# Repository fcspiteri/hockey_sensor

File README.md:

# Hockey Sensor (`HKS`) — Chest-Worn Indoor Ice Hockey Player Tracking System

Production-grade hardware, firmware, and host sensor-fusion suite for a discrete chest-worn indoor ice hockey player tracker (`52.0 × 36.0 × 10.5 mm`, `24.0 g`, IP67) operating **without GPS/GNSS or external rink-side anchors/beacons**.

## Tracked Metrics
- **2D On-Ice Position (`x_m`, `y_m`) & Trajectory Reconstruction** in Rink Frame $R$ (`60.96 × 25.91 m` NHL or `60.0 × 30.0 m` IIHF)
- **Skating Speed & Peak/Mean Speed** (`m/s`, `km/h`)
- **3-Axis Linear Acceleration & High-$g$ Impact Events** ($\pm 16\,g$ strapdown + $\pm 200\,g$ check/impact capture)
- **Shift Detection, On-Ice vs. Bench Gating & Shift Length** (`s`)
- **Total & Per-Shift Distance Skated** (`m`)

---

## Hardware & Industrial Design Renders

### 1. Chest-Worn Enclosure Concept (`52.0 × 36.0 × 10.5 mm`, `24.0 g`, IP67)

### 2. Exploded Assembly Stack-Up (`BT1` 502535 450 mAh LiPo Battery Underneath PCBA)

### 3. Populated 4-Layer PCBA Concept (`38.0 × 28.0 × 0.80 mm`)

### 4. Bare 4-Layer FR4 ENIG PCB Concept & KiCad 3D Raytraced Layout
| Bare 4-Layer PCB Concept | KiCad 3D Raytraced Routed PCB |
| :---: | :---: |
|  |  |

---

## Sample Session Telemetry & Sensor Fusion Output
| Raw Sensor Telemetry (`ICM-42688`, `ADXL372`, `MMC5983MA`, `BMP581`) | Fused Speed, Shifts, Distance & Acceleration |
| :---: | :---: |
|  |  |

---

## Repository Structure

| Path | Description |
| :--- | :--- |
| [`PROJECT_SPEC.md`](PROJECT_SPEC.md) | System requirements, coordinate frames ($R, B, S$), budgets, and validation gates |
| [`INTERFACE_CONTRACT.json`](INTERFACE_CONTRACT.json) | Single source of truth for `.hks` binary flash format, USB/BLE protocol, pinmux, and JSON output schema |
| [`docs/`](docs/) | System architecture (`architecture.md`), contract validator (`validate_contract.py`), and sample telemetry plots (`docs/plots/`) |
| [`hardware/ee/`](hardware/ee/) | Detailed schematic design (`schematic_design.md`), nRF5340 pinmux (`pinmux_and_buses.json`), and EE BOM (`bom.csv`) |
| [`hardware/mechanical/`](hardware/mechanical/) | IP67 PC/TPU + LSR overmolded chest pod specification (`enclosure_spec.md`), dimensions (`dimensions.json`), and mechanical BOM (`bom.csv`) |
| [`hardware/kicad/`](hardware/kicad/) | Routed 4-layer KiCad 8/10 project (`hockey_sensor.kicad_pro`, `hockey_sensor.kicad_sch`, `hockey_sensor.kicad_pcb`), Specctra DSN/SES (`board.dsn`, `board.ses`), DRC report (`drc_report.json`), and turnkey JLCPCB/PCBWay production files (`production/`) |
| [`hardware/power_budget.py`](hardware/power_budget.py) | $0\,^\circ\text{C}$ LiPo battery runtime, flash storage, and mass budget verifier |
| [`firmware/`](firmware/) | Freestanding C11 firmware suite (`libhks_fw.a`), 4096-byte NAND page logger, CRC-32C/SHA-256 integrity, USB CDC-ACM / BLE 5.3 transfer engine, and CLI simulator |
| [`sim/`](sim/) | 400 Hz skating physics truth generator (`physics_sim.py`), `.hks` binary codec (`flash_codec.py`), USB/BLE downloader (`downloader.py`), and 6-layer Error-State EKF + RTS backward smoother (`fusion_pipeline.py`) |
| [`e2e/`](e2e/) | 151-test end-to-end verification suite and 21-check 5-pillar production-readiness rubric (`run_e2e.py`) |

---

## Quick Start & Verification

```zsh
# 1. Validate interface contract & schema parity (27 checks)
python3 docs/validate_contract.py

# 2. Run hardware power, mass, storage, and pinmux unit tests (8 tests)
python3 -m unittest discover -s hardware/tests -v

# 3. Build and test freestanding C11 firmware (13 tests)
make -C firmware test

# 4. Run Python simulation & 6-layer ES-EKF + RTS fusion unit tests (8 tests)
python3 -m unittest discover -s sim/tests -v

# 5. Run full end-to-end test suite & 5-pillar rubric (151 tests, 21 rubric checks)
python3 e2e/run_e2e.py
```

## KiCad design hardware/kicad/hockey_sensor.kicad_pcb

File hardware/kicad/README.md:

# `hockey_sensor` — KiCad 8 Project & Turnkey PCBA Files

This directory contains the generated **KiCad 8/9** design files and turnkey SMT assembly outputs derived directly from [`../ee/schematic_design.md`](../ee/schematic_design.md), [`../ee/pinmux_and_buses.json`](../ee/pinmux_and_buses.json), [`../ee/bom.csv`](../ee/bom.csv), and [`../mechanical/dimensions.json`](../mechanical/dimensions.json).

## Generated Files

| File | Description |
| :--- | :--- |
| [`hockey_sensor.kicad_pro`](./hockey_sensor.kicad_pro) | KiCad 8 project with 4-layer design rules (`0.09 mm` track/space for `aQFN-94`, `90 Ω` USB diff pair, `50 Ω` RF GCPW) |
| [`hockey_sensor.kicad_sch`](./hockey_sensor.kicad_sch) | KiCad 8 schematic (`Eeschema`) containing all 54 component instances (`U1`–`U10`, `J1`, `J2`, `A1`, `Y1`, `Y2`, `L1`–`L6`, `Q1`, `LD1`, `LD2`, `D1`, `D2`, `SW1`, `BT1`, `RT1`, resistors, and capacitors) |
| [`hockey_sensor.kicad_pcb`](./hockey_sensor.kicad_pcb) | KiCad 8 4-layer PCB (`Pcbnew`, `38.0 × 28.0 × 0.80 mm`, ENIG finish) with `Edge.Cuts`, `8.0 × 8.0 mm` 4-layer RF keepout, `M1.4` mounting holes, `In1.Cu`/`B.Cu` `GND` planes, `In2.Cu` `1.8 V` plane, and placed top-side footprints aligned to Sensor Frame `S` ($R_{BS}$) |
| [`hockey_sensor.net`](./hockey_sensor.net) | Complete KiCad S-expression netlist (`64` nets across all isolated SPI/I2C/QSPI/USB/PMIC buses) |
| [`production/hockey_sensor_pcba_bom.csv`](./production/hockey_sensor_pcba_bom.csv) | Turnkey PCBA Bill of Materials formatted for JLCPCB / PCBWay / MacroFab |
| [`production/hockey_sensor_cpl_pick_and_place.csv`](./production/hockey_sensor_cpl_pick_and_place.csv) | Centroid Pick-and-Place (`CPL`) coordinates (`Mid X`, `Mid Y`, `Frame_S_X`, `Frame_S_Y`, `Rotation`, `Layer=top`) |

## How to Open & Route in KiCad 8 / 9

1. Open `hardware/kicad/hockey_sensor.kicad_pro` in **KiCad 8.0+**.
2. Open **PCB Editor (`Pcbnew`)** (`hockey_sensor.kicad_pcb`):
   - Press **`B`** to fill the `In1.Cu` (`GND`), `In2.Cu` (`VDD_1V8`), and `B.Cu` (`GND_SHIELD`) copper zones (they automatically void around the `8.0 × 8.0 mm` top-right RF keepout under `A1`).
   - Route the fanout tracks using the pre-assigned net classes (`0.09–0.12 mm` for `aQFN-94` signal breakout, `0.22 mm / 0.15 mm` differential pair for `USB_D_P`/`USB_D_N`, `0.32 mm` `50 Ω` GCPW for `RF_ANT_OUT` $	o$ `C_RF1`/`L5`/`L6` $	o$ `A1`).
3. Run **Inspect $	o$ Design Rules Checker (DRC)** and export Gerbers + Drill files via **File $	o$ Fabrication Outputs**.

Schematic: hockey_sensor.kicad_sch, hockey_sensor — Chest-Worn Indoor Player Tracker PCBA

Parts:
A1: 2450AT18B0100001E; Johanson_2450AT18B100; MPN 2450AT18B0100001E
BT1: 502535-450mAh-LiPo-Pads; Battery_Pads_3Pin_VBAT_NTC_GND; MPN 502535-450mAh-LiPo
C1, C2, C3, C4, C5, C6, C7, C8, C9, C10, C11, C12, C13, C14, C15, C16, C17, C18: 100nF_10V; C_0402_1005Metric; MPN GRM155R61A104KA01D
C19: 4.7uF_25V_VBUS; C_0603_1608Metric; MPN GRM188R61E475KE11D
C20: 10uF_6.3V_BUCK1; C_0603_1608Metric; MPN GRM188R60J106ME47D
C21: 10uF_6.3V_BUCK2; C_0603_1608Metric; MPN GRM188R60J106ME47D
C22: 4.7uF_10V_DECUSB; C_0603_1608Metric; MPN GRM188R61A475KE15D
C23: 4.7uF_10V_VDD; C_0603_1608Metric; MPN GRM188R61A475KE15D
C24: 4.7uF_10V_DECD; C_0603_1608Metric; MPN GRM188R61A475KE15D
C25: 4.7uF_10V_DECR; C_0603_1608Metric; MPN GRM188R61A475KE15D
C26: 4.7uF_10V_DECA; C_0603_1608Metric; MPN GRM188R61A475KE15D
C27: 1.2pF_C_RF1; C_0402_1005Metric; MPN GJM1555C1H1R2WB01D
C28: 0.8pF_C_RF_SHUNT_DNI; C_0402_1005Metric; MPN GJM1555C1HR80WB01D; not fitted
D1: ESD5Z5.0T1G; D_SOD-523; MPN ESD5Z5.0T1G
D2: BAT54WS; D_SOD-323; MPN BAT54WS
J1: USB4720-03-A; USB_C_Receptacle_GCT_USB4720-03-A_IP67; MPN USB4720-03-A
J2: TC2050-IDC-NL; Tag-Connect_TC2050-IDC-NL_2x05_P1.27mm_Vertical; MPN TC2050-IDC-NL; not fitted
L1, L2: 2.2uH_DFE201610E-2R2M; L_2016_2016Metric; MPN DFE201610E-2R2M
L3: 10uH_LQM18DN100M70L; L_0603_1608Metric; MPN LQM18DN100M70L
L4: 10uH_LQM18DN100M70L; L_0603_1608Metric_Vert; MPN LQM18DN100M70L
L5: 2.7nH_LQW15AN2N7C00D; L_0402_1005Metric_Vert; MPN LQW15AN2N7C00D
L6: 3.3nH_LQW15AN3N3C00D; L_0402_1005Metric; MPN LQW15AN3N3C00D
LD1: LTST-C191KGKT; LED_0603_1608Metric; MPN LTST-C191KGKT
LD2: LTST-C191KRKT; LED_0603_1608Metric; MPN LTST-C191KRKT
MH1, MH2, MH3, MH4: M1.4_Boss; MountingHole_1.5mm_M1.4; MPN M1.4_Boss_NPTH; not fitted
Q1: NTZD3154NT1G; SOT-563; MPN NTZD3154NT1G
R1: 47k_1%_VSET1; R_0402_1005Metric; MPN ERJ-2RKF4702X
R2: 150k_1%_VSET2; R_0402_1005Metric; MPN ERJ-2RKF1503X
R3: 5.1k_1%_CC1; R_0402_1005Metric; MPN ERJ-2RKF5101X
R4: 5.1k_1%_CC2; R_0402_1005Metric; MPN ERJ-2RKF5101X
R5: 4.7k_I2C0_SDA; R_0402_1005Metric; MPN ERJ-2GEJ472X
R6: 4.7k_I2C0_SCL; R_0402_1005Metric; MPN ERJ-2GEJ472X
R7: 4.7k_I2C2_SDA; R_0402_1005Metric; MPN ERJ-2GEJ472X
R8: 4.7k_I2C2_SCL; R_0402_1005Metric; MPN ERJ-2GEJ472X
R9: 10k_CS_IMU; R_0402_1005Metric; MPN ERJ-2GEJ103X
R10: 10k_CS_HIGHG; R_0402_1005Metric; MPN ERJ-2GEJ103X
R11: 10k_CS_FLASH; R_0402_1005Metric; MPN ERJ-2GEJ103X
R12: 100k_GATE_G; R_0402_1005Metric; MPN ERJ-2GEJ104X
R13: 100k_GATE_R; R_0402_1005Metric; MPN ERJ-2GEJ104X
R14: 100k_BTN_PU; R_0402_1005Metric; MPN ERJ-2GEJ104X
R15: 4.7k_3V0_SDA; R_0402_1005Metric; MPN ERJ-2GEJ472X
R16: 4.7k_3V0_SCL; R_0402_1005Metric; MPN ERJ-2GEJ472X
R17: 200k_PCA_EN; R_0402_1005Metric; MPN ERJ-2GEJ204X
R18: 1k_LED_G; R_0402_1005Metric; MPN ERJ-2GEJ102X
R19: 1k_LED_R; R_0402_1005Metric; MPN ERJ-2GEJ102X
RT1: 10k_NTC_DNI; R_0402_1005Metric; MPN NCP15XH103F03RC; not fitted
SW1: EVPAWCD4A; SW_SPST_EVPAW; MPN EVPAWCD4A
U1: nRF5340-QKAA; Nordic_AQFN-94-1EP_7x7mm_P0.4mm; MPN nRF5340-QKAA-R7
U2: nPM1300-QEAA-R; QFN-32-1EP_5x5mm_P0.5mm; MPN nPM1300-QEAA-R
U3: ICM-42688-P; LGA-14_2.5x3.0mm_P0.5mm; MPN ICM-42688-P
U4: ADXL372BCCZ-RL7; LGA-16_3.0x3.25mm_P0.5mm; MPN ADXL372BCCZ-RL7
U5: MMC5983MA; LGA-16_3.0x3.0mm_P0.5mm; MPN MMC5983MA
U6: BMP581; LGA-10_2.0x2.0mm_P0.5mm; MPN BMP581
U7: W25N01JWZEIG; WSON-8-1EP_8x6mm_P1.27mm; MPN W25N01JWZEIG
U8: PCA9306DCUR; VSSOP-8_2.3x2mm_P0.5mm; MPN PCA9306DCUR
U9: SN74AXC1T45DRLR; SOT-563; MPN SN74AXC1T45DRLR
U10: TPD4E05U06DQAR; USON-10_2.5x1.0mm_P0.5mm; MPN TPD4E05U06DQAR
Y1: NX2016SA-32MHz; Crystal_SMD_2016-4Pin_2.0x1.6mm; MPN NX2016SA-32MHz
Y2: FC-12M-32.768K-20ppm; Crystal_SMD_2012-2Pin_2.0x1.2mm; MPN FC-12M-32.768K-20ppm

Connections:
/ADXL_BYP: C14.1 (ADXL_BYP), U4.2 (ADXL_BYP)
/ADXL_INT1_P0.06: U1.AB2 (ADXL_INT1_P0.06), U4.11 (ADXL_INT1_P0.06)
/ADXL_INT2_P0.07: U1.AD2 (ADXL_INT2_P0.07), U4.9 (ADXL_INT2_P0.07)
/BARO_INT_P1.04: U1.AL19 (BARO_INT_P1.04), U6.7 (BARO_INT_P1.04)
/BTN_USER_N_P1.06: D2.2 (BTN_USER_N_P1.06), R14.1 (BTN_USER_N_P1.06), U1.AL21 (BTN_USER_N_P1.06)
/DECA: C26.1 (DECA), U1.A13 (DECA)
/DECD: C24.1 (DECD), L3.2 (DECD), U1.A15 (DECD)
/DECN: C1.1 (DECN), U1.A23 (DECN)
/DECR: C25.1 (DECR), L4.2 (DECR), U1.A27 (DECR)
/DECRF: C2.1 (DECRF), U1.G31 (DECRF)
/DECUSB: C22.1 (DECUSB), U1.B6 (DECUSB)
/GND: BT1.3 (GND), C1.2 (GND), C2.2 (GND), C3.2 (GND), C4.2 (GND), C5.2 (GND), C6.2 (GND), C7.2 (GND), C8.2 (GND), C9.2 (GND), C10.2 (GND), C11.2 (GND), C12.2 (GND), C13.2 (GND), C14.2 (GND), C15.2 (GND), C16.2 (GND), C17.2 (GND), C18.2 (GND), C19.2 (GND), C20.2 (GND), C21.2 (GND), C22.2 (GND), C23.2 (GND), C24.2 (GND), C25.2 (GND), C26.2 (GND), C28.1 (GND), D1.2 (GND), J1.A1 (GND), J1.B1 (GND), J1.S1 (GND), J1.S2 (GND), J2.3 (GND), J2.5 (GND), J2.9 (GND), L5.2 (GND), Q1.1 (GND), Q1.4 (GND), R1.2 (GND), R2.2 (GND), R3.2 (GND), R4.2 (GND), R12.2 (GND), R13.2 (GND), RT1.2 (GND), SW1.2 (GND), U1.A25 (GND), U1.AG31 (GND), U1.B12 (GND), U1.B26 (GND), U1.D2 (GND), U1.EP (GND), U1.F2 (GND), U1.G1 (GND), U1.H2 (GND), U1.J31 (GND), U1.K2 (GND), U1.T2 (GND), U2.2 (GND), U2.6 (GND), U2.EP (GND), U3.6 (GND), U3.7 (GND), U3.10 (GND), U3.11 (GND), U4.5 (GND), U4.12 (GND), U4.13 (GND), U4.15 (GND), U5.6 (GND), U5.9 (GND), U5.11 (GND), U6.3 (GND), U6.8 (GND), U6.9 (GND), U7.4 (GND), U7.9 (GND), U8.1 (GND), U9.2 (GND), U9.5 (GND), U10.3 (GND), U10.8 (GND), Y1.2 (GND), Y1.4 (GND)
/HFXO_XC1: U1.C31 (HFXO_XC1), Y1.1 (HFXO_XC1)
/HFXO_XC2: U1.B30 (HFXO_XC2), Y1.3 (HFXO_XC2)
/I2C0_SCL_1V8_P1.03: R6.1 (I2C0_SCL_1V8_P1.03), U1.AF2 (I2C0_SCL_1V8_P1.03), U6.2 (I2C0_SCL_1V8_P1.03), U8.3 (I2C0_SCL_1V8_P1.03)
/I2C0_SCL_3V0: R16.1 (I2C0_SCL_3V0), U5.1 (I2C0_SCL_3V0), U8.6 (I2C0_SCL_3V0)
/I2C0_SDA_1V8_P1.02: R5.1 (I2C0_SDA_1V8_P1.02), U1.AE1 (I2C0_SDA_1V8_P1.02), U6.4 (I2C0_SDA_1V8_P1.02), U8.4 (I2C0_SDA_1V8_P1.02)
/I2C0_SDA_3V0: R15.1 (I2C0_SDA_3V0), U5.5 (I2C0_SDA_3V0), U8.5 (I2C0_SDA_3V0)
/I2C2_PMIC_SCL_P0.24: R8.1 (I2C2_PMIC_SCL_P0.24), U1.AL27 (I2C2_PMIC_SCL_P0.24), U2.14 (I2C2_PMIC_SCL_P0.24)
/I2C2_PMIC_SDA_P0.23: R7.1 (I2C2_PMIC_SDA_P0.23), U1.AK20 (I2C2_PMIC_SDA_P0.23), U2.13 (I2C2_PMIC_SDA_P0.23)
/IMU_INT1_P0.04: U1.V2 (IMU_INT1_P0.04), U3.4 (IMU_INT1_P0.04)
/IMU_INT2_P0.05: U1.Y2 (IMU_INT2_P0.05), U3.9 (IMU_INT2_P0.05)
/LED_G_ANODE: LD1.1 (LED_G_ANODE), R18.2 (LED_G_ANODE)
/LED_G_CATHODE: LD1.2 (LED_G_CATHODE), Q1.6 (LED_G_CATHODE)
/LED_G_GATE_P1.07: Q1.2 (LED_G_GATE_P1.07), R12.1 (LED_G_GATE_P1.07), U1.AK24 (LED_G_GATE_P1.07)
/LED_R_ANODE: LD2.1 (LED_R_ANODE), R19.2 (LED_R_ANODE)
/LED_R_CATHODE: LD2.2 (LED_R_CATHODE), Q1.3 (LED_R_CATHODE)
/LED_R_GATE_P1.08: Q1.5 (LED_R_GATE_P1.08), R13.1 (LED_R_GATE_P1.08), U1.AL23 (LED_R_GATE_P1.08)
/LFXO_XL1_P0.00: U1.N1 (LFXO_XL1_P0.00), Y2.1 (LFXO_XL1_P0.00)
/LFXO_XL2_P0.01: U1.R1 (LFXO_XL2_P0.01), Y2.2 (LFXO_XL2_P0.01)
/MAG_INT_1V8_P1.01: U1.P2 (MAG_INT_1V8_P1.01), U9.3 (MAG_INT_1V8_P1.01)
/MAG_INT_3V0: U5.15 (MAG_INT_3V0), U9.4 (MAG_INT_3V0)
/MMC_CAP: C17.1 (MMC_CAP), U5.10 (MMC_CAP)
/NRESET: J2.10 (NRESET), U1.AC31 (NRESET)
/NRF_DCC: L4.1 (NRF_DCC), U1.A21 (NRF_DCC)
/NRF_DCCD: L3.1 (NRF_DCCD), U1.B10 (NRF_DCCD)
/PCA9306_EN: C18.1 (PCA9306_EN), R17.1 (PCA9306_EN), U8.7 (PCA9306_EN), U8.8 (PCA9306_EN)
/PMIC_INT_P1.05: U1.AK22 (PMIC_INT_P1.05), U2.7 (PMIC_INT_P1.05)
/PMIC_NTC: BT1.2 (PMIC_NTC), RT1.1 (PMIC_NTC), U2.18 (PMIC_NTC)
/PMIC_SHPHLD: D2.1 (PMIC_SHPHLD), SW1.1 (PMIC_SHPHLD), U2.15 (PMIC_SHPHLD)
/PMIC_VSET1: R1.1 (PMIC_VSET1), U2.17 (PMIC_VSET1)
/PMIC_VSET2: R2.1 (PMIC_VSET2), U2.16 (PMIC_VSET2)
/QSPI_CS_N_P0.18: R11.1 (QSPI_CS_N_P0.18), U1.AK14 (QSPI_CS_N_P0.18), U7.1 (QSPI_CS_N_P0.18)
/QSPI_IO0_MOSI_P0.13: U1.AL5 (QSPI_IO0_MOSI_P0.13), U7.5 (QSPI_IO0_MOSI_P0.13)
/QSPI_IO1_MISO_P0.14: U1.AK8 (QSPI_IO1_MISO_P0.14), U7.2 (QSPI_IO1_MISO_P0.14)
/QSPI_IO2_WP_P0.15: U1.AK10 (QSPI_IO2_WP_P0.15), U7.3 (QSPI_IO2_WP_P0.15)
/QSPI_IO3_HOLD_P0.16: U1.AL9 (QSPI_IO3_HOLD_P0.16), U7.7 (QSPI_IO3_HOLD_P0.16)
/QSPI_SCK_P0.17: U1.AK12 (QSPI_SCK_P0.17), U7.6 (QSPI_SCK_P0.17)
/RF_ANT_FEED: A1.1 (RF_ANT_FEED), L6.2 (RF_ANT_FEED)
/RF_ANT_OUT: C27.1 (RF_ANT_OUT), C28.2 (RF_ANT_OUT), U1.L31 (RF_ANT_OUT)
/RF_MATCH_MID: C27.2 (RF_MATCH_MID), L5.1 (RF_MATCH_MID), L6.1 (RF_MATCH_MID)
/SPI1_CS_HIGHG_N_P0.22: R10.1 (SPI1_CS_HIGHG_N_P0.22), U1.AK18 (SPI1_CS_HIGHG_N_P0.22), U4.8 (SPI1_CS_HIGHG_N_P0.22)
/SPI1_MISO_P0.21: U1.AL15 (SPI1_MISO_P0.21), U4.7 (SPI1_MISO_P0.21)
/SPI1_MOSI_P0.20: U1.AK16 (SPI1_MOSI_P0.20), U4.6 (SPI1_MOSI_P0.20)
/SPI1_SCK_P0.19: U1.AL13 (SPI1_SCK_P0.19), U4.4 (SPI1_SCK_P0.19)
/SPI4_CS_IMU_N_P0.11: R9.1 (SPI4_CS_IMU_N_P0.11), U1.AK4 (SPI4_CS_IMU_N_P0.11), U3.12 (SPI4_CS_IMU_N_P0.11)
/SPI4_MISO_P0.10: U1.AK2 (SPI4_MISO_P0.10), U3.1 (SPI4_MISO_P0.10)
/SPI4_MOSI_P0.09: U1.AJ1 (SPI4_MOSI_P0.09), U3.14 (SPI4_MOSI_P0.09)
/SPI4_SCK_P0.08: U1.AH2 (SPI4_SCK_P0.08), U3.13 (SPI4_SCK_P0.08)
/SW1_BUCK1: L1.1 (SW1_BUCK1), U2.3 (SW1_BUCK1)
/SW2_BUCK2: L2.1 (SW2_BUCK2), U2.5 (SW2_BUCK2)
/SWDCLK: J2.4 (SWDCLK), U1.W31 (SWDCLK)
/SWDIO: J2.2 (SWDIO), U1.AA31 (SWDIO)
/USB_CC1: J1.A5 (USB_CC1), R3.1 (USB_CC1), U10.4 (USB_CC1), U10.7 (USB_CC1)
/USB_CC2: J1.B5 (USB_CC2), R4.1 (USB_CC2), U10.5 (USB_CC2), U10.6 (USB_CC2)
/USB_D_N: J1.A7 (USB_D_N), J1.B7 (USB_D_N), U1.B4 (USB_D_N), U10.2 (USB_D_N), U10.9 (USB_D_N)
/USB_D_P: J1.A6 (USB_D_P), J1.B6 (USB_D_P), U1.B2 (USB_D_P), U10.1 (USB_D_P), U10.10 (USB_D_P)
/VBAT: BT1.1 (VBAT), U2.19 (VBAT)
/VBUS_5V: C19.1 (VBUS_5V), D1.1 (VBUS_5V), J1.A4 (VBUS_5V), J1.B4 (VBUS_5V), U1.A5 (VBUS_5V), U2.21 (VBUS_5V), U2.22 (VBUS_5V)
/VDD_1V8: C3.1 (VDD_1V8), C4.1 (VDD_1V8), C5.1 (VDD_1V8), C6.1 (VDD_1V8), C7.1 (VDD_1V8), C8.1 (VDD_1V8), C9.1 (VDD_1V8), C10.1 (VDD_1V8), C11.1 (VDD_1V8), C12.1 (VDD_1V8), C13.1 (VDD_1V8), C20.1 (VDD_1V8), C23.1 (VDD_1V8), J2.1 (VDD_1V8), L1.2 (VDD_1V8), R5.2 (VDD_1V8), R6.2 (VDD_1V8), R7.2 (VDD_1V8), R8.2 (VDD_1V8), R9.2 (VDD_1V8), R10.2 (VDD_1V8), R11.2 (VDD_1V8), R14.2 (VDD_1V8), U1.A19 (VDD_1V8), U1.AC1 (VDD_1V8), U1.AG1 (VDD_1V8), U1.AJ31 (VDD_1V8), U1.AL3 (VDD_1V8), U1.AL7 (VDD_1V8), U1.AL11 (VDD_1V8), U1.AL17 (VDD_1V8), U1.AL25 (VDD_1V8), U1.B8 (VDD_1V8), U1.B28 (VDD_1V8), U1.C1 (VDD_1V8), U1.E1 (VDD_1V8), U1.E31 (VDD_1V8), U1.L1 (VDD_1V8), U1.N31 (VDD_1V8), U1.U1 (VDD_1V8), U2.1 (VDD_1V8), U2.12 (VDD_1V8), U3.5 (VDD_1V8), U3.8 (VDD_1V8), U4.1 (VDD_1V8), U4.14 (VDD_1V8), U4.16 (VDD_1V8), U6.1 (VDD_1V8), U6.5 (VDD_1V8), U6.6 (VDD_1V8), U6.10 (VDD_1V8), U7.8 (VDD_1V8), U8.2 (VDD_1V8), U9.1 (VDD_1V8)
/VDD_3V0: C15.1 (VDD_3V0), C16.1 (VDD_3V0), C21.1 (VDD_3V0), L2.2 (VDD_3V0), R15.2 (VDD_3V0), R16.2 (VDD_3V0), R17.2 (VDD_3V0), R18.1 (VDD_3V0), R19.1 (VDD_3V0), U2.32 (VDD_3V0), U5.2 (VDD_3V0), U5.4 (VDD_3V0), U5.13 (VDD_3V0), U9.6 (VDD_3V0)
/VSYS: U2.4 (VSYS), U2.20 (VSYS)

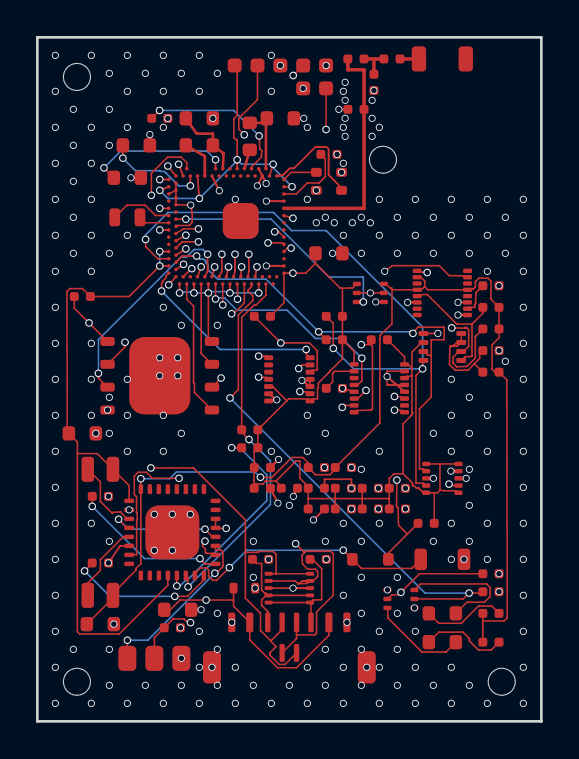
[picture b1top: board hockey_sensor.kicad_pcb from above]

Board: 4 copper layers, 28.0 x 38.0 mm, 80 parts (0 on the bottom side), 72 nets.

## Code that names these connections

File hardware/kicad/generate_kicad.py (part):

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        "10": "USB_D_P",
    }
    # Q1: NTZD3154NT1G Dual N-MOSFET SOT-563 (Exact onsemi NTZD3154N Datasheet Pinout)
    #   Pin 1=S1(GND), Pin 2=G1(LED_G_GATE_P1.07), Pin 3=D2(LED_R_CATHODE),
    #   Pin 4=S2(GND), Pin 5=G2(LED_R_GATE_P1.08), Pin 6=D1(LED_G_CATHODE)
    q1_nets = {
        "1": "GND",
        "2": "LED_G_GATE_P1.07",
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    c100n_nets = {
        0: "DECN",       # C1: nRF5340 Ball A23 DECN 100nF to GND
        1: "DECRF",      # C2: nRF5340 Ball G31 DECRF 100nF to GND
        13: "ADXL_BYP",  # C14: ADXL372 Pin 2 BYP 100nF to GND (M3)
        14: "VDD_3V0",   # C15: 3.0V local decoupling
        15: "VDD_3V0",   # C16: 3.0V local decoupling
        16: "MMC_CAP",   # C17: MMC5983MA Pin 10 CAP 100nF to GND (M4)
        17: "PCA9306_EN",# C18: PCA9306 VREF2/EN 100nF filter cap to GND
    }
    c100n_coords = {
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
